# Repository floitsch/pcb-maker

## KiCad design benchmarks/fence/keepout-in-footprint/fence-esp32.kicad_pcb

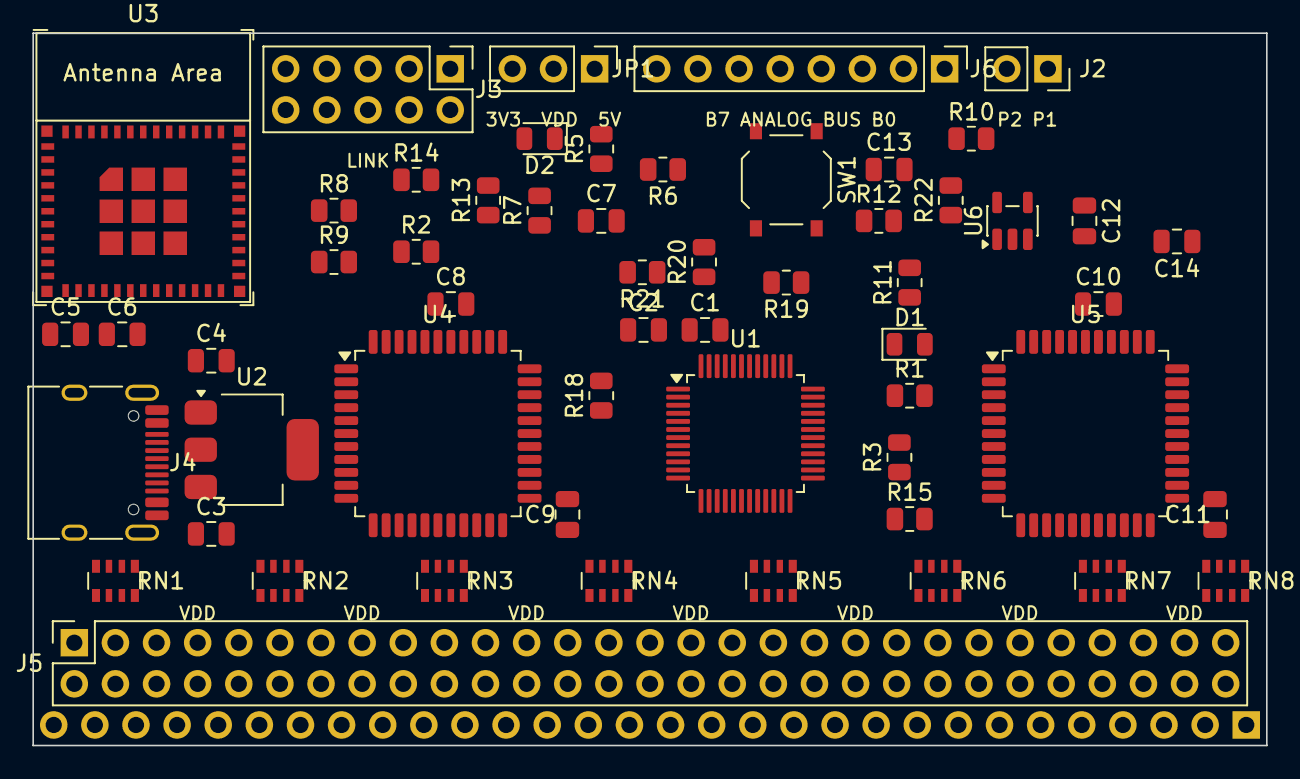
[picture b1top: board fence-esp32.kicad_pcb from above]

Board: 2 copper layers, 76.2 x 44.0 mm, 57 parts (1 on the bottom side), 107 nets, no tracks yet.

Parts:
C1, C6, C8, C9, C10, C11: 100n; C_0805_2012Metric
C2, C3, C4, C5, C7, C12, C13, C14: 10u; C_0805_2012Metric
D1, D2: LED; LED_0805_2012Metric
J1: Breadboard rows; PinHeader_1x30_P2.54mm_Vertical
J2: Ports; PinSocket_1x02_P2.54mm_Vertical
J3: Link; PinHeader_2x05_P2.54mm_Vertical
J4: USB-C; USB_C_Receptacle_HRO_TYPE-C-31-M-12
J5: Rails; PinSocket_2x29_P2.54mm_Vertical
J6: Bus; PinHeader_1x08_P2.54mm_Vertical
JP1: VDD 5V|3V3; PinHeader_1x03_P2.54mm_Vertical
R1, R2, R3, R5, R6, R7, R8, R9, R10, R11, R13, R14, R15, R18, R19, R20, R21, R22: 10k; R_0805_2012Metric
R12: 1M; R_0805_2012Metric
RN1, RN2, RN3, RN4, RN5, RN6, RN7, RN8: 1k; R_Array_Convex_4x0603
SW1: BOOT; SW_Push_1P1T_XKB_TS-1187A
U1: CH32X035C8T6; LQFP-48_7x7mm_P0.5mm
U2: AMS1117-3.3; SOT-223-3_TabPin2
U3: ESP32-C3-MINI-1
U4, U5: CH446Q; LQFP-44_10x10mm_P0.8mm
U6: TPS60401DBV; SOT-23-5

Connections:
/+3V3: C4.1, C5.1, C6.1, J3.3, JP1.3, R5.2, R6.2, R7.2, R8.2, R9.2, R10.2, U2.2, U3.3
/BUS0: J6.1, U4.33, U5.33
/BUS1: J6.2, U4.35, U5.35
/BUS2: J6.3, U4.37, U5.37
/BUS3: J6.4, U4.39, U5.39
/BUS4: J6.5, U4.17, U5.17
/BUS5: J6.6, U4.15, U5.15
/BUS6: J6.7, U4.13, U5.13
/BUS7: J6.8, RN8.6, U4.11, U5.11
/CC1: J4.A5, R2.1, R14.1
/CC2: J4.B5, R3.1, R15.1
/CFLY_N: C12.2, U6.3
/CFLY_P: C12.1, U6.5
/CH32_BOOT: R11.2, R12.1, U1.33
/ESP_CH32_BOOT: R11.1, U3.16
/ESP_EN: C7.1, R7.1, U3.8
/ESP_IO2: R8.1, U3.5
/ESP_IO8: R9.1, U3.22
/ESP_IO9: R10.1, SW1.2, U3.23
/ESP_LED: R13.1, U3.6
/ESP_LED_A: D2.2, R13.2
/GND: C1.2, C2.2, C3.2, C4.2, C5.2, C6.2, C7.2, C8.2, C9.2, C10.2, C11.2, C13.2, C14.1, D1.1, D2.1, J3.2, J3.4, J4.A1, J4.A12, J4.B1, J4.B12, J4.SH, J5.2, J5.4, J5.6, J5.8, J5.10, J5.12, J5.14, J5.16, J5.18, J5.20, J5.22, J5.24, J5.26, J5.28, J5.30, J5.32, J5.34, J5.36, J5.38, J5.40, J5.42, J5.44, J5.46, J5.48, J5.50, J5.52, J5.54, J5.56, J5.58, R2.2, R3.2, R12.2, R14.2, R15.2, SW1.1, U1.47, U2.1, U3.1, U3.2, U3.11, U3.14, U3.36, U3.37, U3.38, U3.39, U3.40, U3.41, U3.42, U3.43, U3.44, U3.45, U3.46, U3.47, U3.48, U3.49, U3.50, U3.51, U3.52, U3.53, U4.10, U4.12, U4.18, U4.19, U4.20, U4.21, U4.40, U4.42, U4.43, U5.10, U5.12, U5.18, U5.19, U5.20, U5.21, U5.40, U5.42, U5.43, U6.4
/LED: R1.1, U1.36
/LED_A: D1.2, R1.2
/LINK0: J3.9, R20.2, U3.12
/LINK1: J3.10, R21.2, U3.13
/LINK_SWCLK: J3.8, R19.2, U3.21
/LINK_SWDIO: J3.7, R18.2, U3.20
/MCU_LINK0: R20.1, U1.40
/MCU_LINK1: R21.1, U1.41
/MCU_PROBE: RN8.3, U1.21
/MCU_ROW1: RN1.4, U1.1
/MCU_ROW2: RN1.3, U1.2
/MCU_ROW3: RN1.2, U1.3
/MCU_ROW4: RN1.1, U1.4
/MCU_ROW5: RN2.4, U1.5
/MCU_ROW6: RN2.3, U1.6
/MCU_ROW7: RN2.2, U1.7
/MCU_ROW8: RN2.1, U1.8
/MCU_ROW9: RN3.4, U1.9
/MCU_ROW10: RN3.3, U1.10
/MCU_ROW11: RN3.2, U1.11
/MCU_ROW12: RN3.1, U1.12
/MCU_ROW13: RN4.4, U1.13
/MCU_ROW14: RN4.3, U1.14
/MCU_ROW15: RN4.2, U1.15
/MCU_ROW16: RN4.1, U1.16
/MCU_ROW17: RN5.4, U1.17
/MCU_ROW18: RN5.3, U1.18
/MCU_ROW19: RN5.2, U1.19
/MCU_ROW20: RN5.1, U1.20
/MCU_ROW21: RN6.4, U1.22
/MCU_ROW22: RN6.3, U1.23
/MCU_ROW23: RN6.2, U1.24
/MCU_ROW24: RN6.1, U1.25
/MCU_ROW25: RN7.4, U1.26
/MCU_ROW26: RN7.3, U1.27
/MCU_ROW27: RN7.2, U1.28
/MCU_ROW28: RN7.1, U1.29
/MCU_ROW29: RN8.2, U1.30
/MCU_ROW30: RN8.1, U1.31
/PORT1: J2.1, U5.30
/PORT2: J2.2, U5.31
/ROW1: J1.30, RN1.5, U4.1
/ROW2: J1.29, RN1.6, U4.2
/ROW3: J1.28, RN1.7, U4.3
/ROW4: J1.27, RN1.8, U4.4
/ROW5: J1.26, RN2.5, U4.5
/ROW6: J1.25, RN2.6, U4.6
/ROW7: J1.24, RN2.7, U4.7
/ROW8: J1.23, RN2.8, U4.8
/ROW9: J1.22, RN3.5, U4.24
/ROW10: J1.21, RN3.6, U4.25
/ROW11: J1.20, RN3.7, U4.26
/ROW12: J1.19, RN3.8, U4.27
/ROW13: J1.18, RN4.5, U4.28
/ROW14: J1.17, RN4.6, U4.29
/ROW15: J1.16, RN4.7, U4.30
/ROW16: J1.15, RN4.8, U4.31
/ROW17: J1.14, RN5.5, U5.1
/ROW18: J1.13, RN5.6, U5.2
/ROW19: J1.12, RN5.7, U5.3
/ROW20: J1.11, RN5.8, U5.4
/ROW21: J1.10, RN6.5, U5.5
/ROW22: J1.9, RN6.6, U5.6
/ROW23: J1.8, RN6.7, U5.7
/ROW24: J1.7, RN6.8, U5.8
/ROW25: J1.6, RN7.5, U5.24
/ROW26: J1.5, RN7.6, U5.25
/ROW27: J1.4, RN7.7, U5.26
/ROW28: J1.3, RN7.8, U5.27
/ROW29: J1.2, RN8.7, U5.28
/ROW30: J1.1, RN8.8, U5.29
/SCL: J3.6, R6.1, U1.42, U3.19
/SDA: J3.5, R5.1, U1.43, U3.18
/SWCLK: R19.1, U1.37
/SWDIO: R18.1, U1.34
/USB_DM: J4.A7, J4.B7, U3.26
/USB_DP: J4.A6, J4.B6, U3.27
/VBUS: C3.1, C8.1, C10.1, C13.1, J3.1, J4.A4, J4.A9, J4.B4, J4.B9, JP1.1, U2.3, U4.38, U5.38, U6.2
/VDD: C1.1, C2.1, J5.1, J5.3, J5.5, J5.7, J5.9, J5.11, J5.13, J5.15, J5.17, J5.19, J5.21, J5.23, J5.25, J5.27, J5.29, J5.31, J5.33, J5.35, J5.37, J5.39, J5.41, J5.43, J5.45, J5.47, J5.49, J5.51, J5.53, J5.55, J5.57, JP1.2, R22.2, U1.48
/VEE: C9.1, C11.1, C14.2, U4.16, U5.16, U6.1
/XP_CK: U1.38, U4.34, U5.34
/XP_DAT: U1.35, U4.36, U5.36
/XP_RST: R22.1, U1.45, U4.41, U5.41
/XP_STB_A: U1.39, U4.14
/XP_STB_B: U1.44, U5.14
